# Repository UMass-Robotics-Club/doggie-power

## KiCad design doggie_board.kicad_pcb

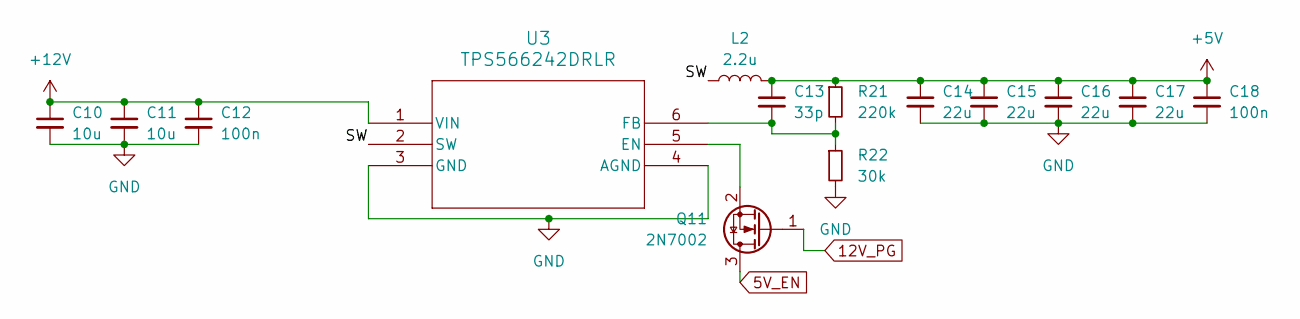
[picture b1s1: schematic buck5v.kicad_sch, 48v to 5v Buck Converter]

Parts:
C10, C11: 10u; C_0603_1608Metric_Pad1.08x0.95mm_HandSolder
C12, C18: 100n; C_0603_1608Metric_Pad1.08x0.95mm_HandSolder
C13: 33p; C_0603_1608Metric_Pad1.08x0.95mm_HandSolder
C14, C15, C16, C17: 22u; C_0603_1608Metric_Pad1.08x0.95mm_HandSolder
L2: 2.2u; IND_1217AS-H-2R2N=P3
Q11: 2N7002; SOT-23
R21: 220k; R_0603_1608Metric_Pad0.98x0.95mm_HandSolder
R22: 30k; R_0603_1608Metric_Pad0.98x0.95mm_HandSolder
U3: TPS566242DRLR; SOT5x3_DRL_TEX

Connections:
5V_EN: Q11.3 (D); also elsewhere on the board
12V_PG: Q11.1 (G); also elsewhere on the board
+5V: C13.1, C14.1, C15.1, C16.1, C17.1, C18.1, L2.2, R21.1; also elsewhere on the board
+12V: C10.1, C11.1, C12.1, U3.1 (VIN); also elsewhere on the board
/5v Buck Converter/SW: L2.1, U3.2 (SW)
GND: C10.2, C11.2, C12.2, C14.2, C15.2, C16.2, C17.2, C18.2, R22.2, U3.3 (GND), U3.4 (AGND); also elsewhere on the board
unnamed: Q11.2 (S), U3.5 (EN)
unnamed: C13.2, R21.2, R22.1, U3.6 (FB)

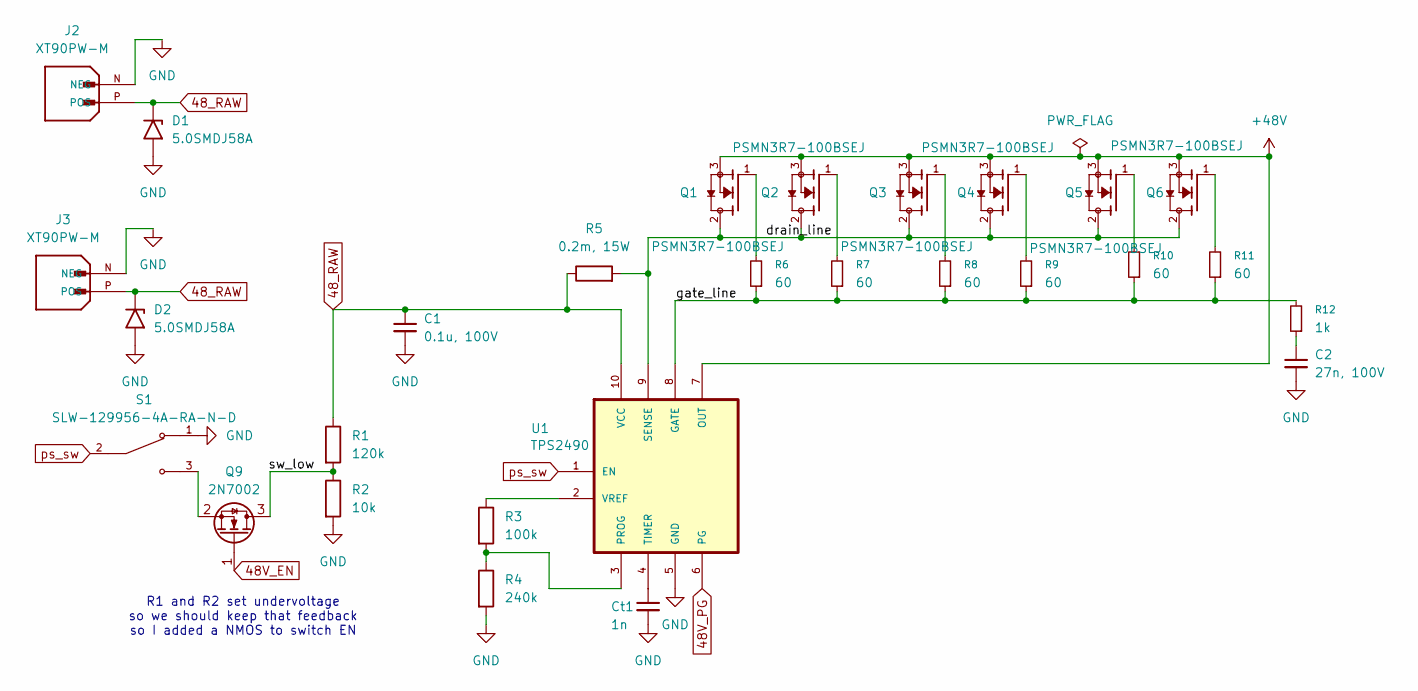
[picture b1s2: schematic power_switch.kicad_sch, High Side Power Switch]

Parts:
C1: 0.1u, 100V; C_0603_1608Metric_Pad1.08x0.95mm_HandSolder
C2: 27n, 100V; C_0603_1608Metric_Pad1.08x0.95mm_HandSolder
Ct1: 1n; C_0603_1608Metric_Pad1.08x0.95mm_HandSolder
D1, D2: 5.0SMDJ58A; D_SMB-SMC_Universal_Handsoldering
J2, J3: XT90PW-M; AMASS_XT90PW-M; PARTREV V00
Q1, Q2, Q3, Q4, Q5, Q6: PSMN3R7-100BSEJ; D2PAK_NEX; PARTREV 3 September 2018
Q9: 2N7002; SOT-23
R1: 120k; R_0603_1608Metric_Pad0.98x0.95mm_HandSolder
R2: 10k; R_0603_1608Metric_Pad0.98x0.95mm_HandSolder
R3: 100k; R_0603_1608Metric_Pad0.98x0.95mm_HandSolder
R4: 240k; R_0603_1608Metric_Pad0.98x0.95mm_HandSolder
R5: 0.2m, 15W; RES_PSR500_ROM
R6, R7, R8, R9, R10, R11: 60; R_0603_1608Metric_Pad0.98x0.95mm_HandSolder
R12: 1k; R_0603_1608Metric_Pad0.98x0.95mm_HandSolder
S1: SLW-129956-4A-RA-N-D; SW_SLW-129956-4A-RA-N-D; PARTREV 1.01
U1: TPS2490; VSSOP-10_3x3mm_P0.5mm

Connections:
48V_EN: Q9.1 (G); also elsewhere on the board
48V_PG: U1.6 (PG); also elsewhere on the board
48_RAW: C1.1, D1.1 (A1), D2.1 (A1), J2.P (POS), J3.P (POS), R1.1, R5.1, U1.10 (VCC); also elsewhere on the board
+48V: Q1.3, Q2.3, Q3.3, Q4.3, Q5.3, Q6.3, U1.7 (OUT); also elsewhere on the board
/High Side Power Switch/drain_line: Q1.2, Q2.2, Q3.2, Q4.2, Q5.2, Q6.2, R5.2, U1.9 (SENSE)
/High Side Power Switch/gate_line: R6.1, R7.1, R8.1, R9.1, R10.1, R11.1, R12.2, U1.8 (GATE)
/High Side Power Switch/sw_low: Q9.3 (D), R1.2, R2.1
GND: C1.2, C2.2, Ct1.2, D1.2 (A2), D2.2 (A2), J2.N (NEG), J3.N (NEG), R2.2, R4.2, S1.1, U1.5 (GND); also elsewhere on the board
unnamed: C2.1, R12.1
unnamed: Q1.1, R6.2
unnamed: Q2.1, R7.2
unnamed: Q3.1, R8.2
unnamed: Q4.1, R9.2
unnamed: Q5.1, R10.2
unnamed: Q6.1, R11.2
unnamed: Q9.2 (S), S1.3
unnamed: R3.2, R4.1, U1.3 (PROG)
unnamed: Ct1.1, U1.4 (TIMER)
unnamed: R3.1, U1.2 (VREF)
ps_sw: S1.2, U1.1 (EN)

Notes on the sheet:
R1 and R2 set undervoltage so we should keep that feedback so I added a NMOS to switch EN

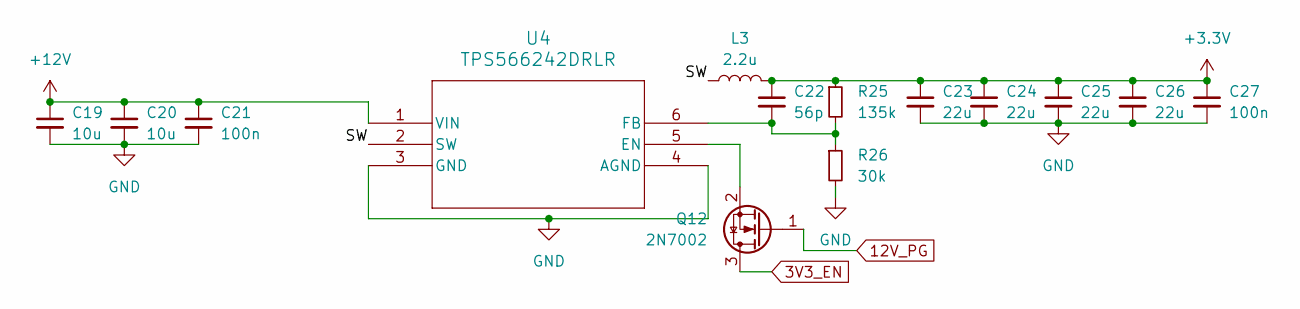
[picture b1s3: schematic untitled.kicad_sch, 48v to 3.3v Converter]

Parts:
C19, C20: 10u; C_0603_1608Metric_Pad1.08x0.95mm_HandSolder
C21, C27: 100n; C_0603_1608Metric_Pad1.08x0.95mm_HandSolder
C22: 56p; C_0603_1608Metric_Pad1.08x0.95mm_HandSolder
C23, C24, C25, C26: 22u; C_0603_1608Metric_Pad1.08x0.95mm_HandSolder
L3: 2.2u; IND_1217AS-H-2R2N=P3
Q12: 2N7002; SOT-23
R25: 135k; R_0603_1608Metric_Pad0.98x0.95mm_HandSolder
R26: 30k; R_0603_1608Metric_Pad0.98x0.95mm_HandSolder
U4: TPS566242DRLR; SOT5x3_DRL_TEX

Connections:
3V3_EN: Q12.3 (D); also elsewhere on the board
12V_PG: Q12.1 (G); also elsewhere on the board
+3.3V: C22.1, C23.1, C24.1, C25.1, C26.1, C27.1, L3.2, R25.1; also elsewhere on the board
+12V: C19.1, C20.1, C21.1, U4.1 (VIN); also elsewhere on the board
/3.3v Buck Converter/SW: L3.1, U4.2 (SW)
GND: C19.2, C20.2, C21.2, C23.2, C24.2, C25.2, C26.2, C27.2, R26.2, U4.3 (GND), U4.4 (AGND); also elsewhere on the board
unnamed: Q12.2 (S), U4.5 (EN)
unnamed: C22.2, R25.2, R26.1, U4.6 (FB)

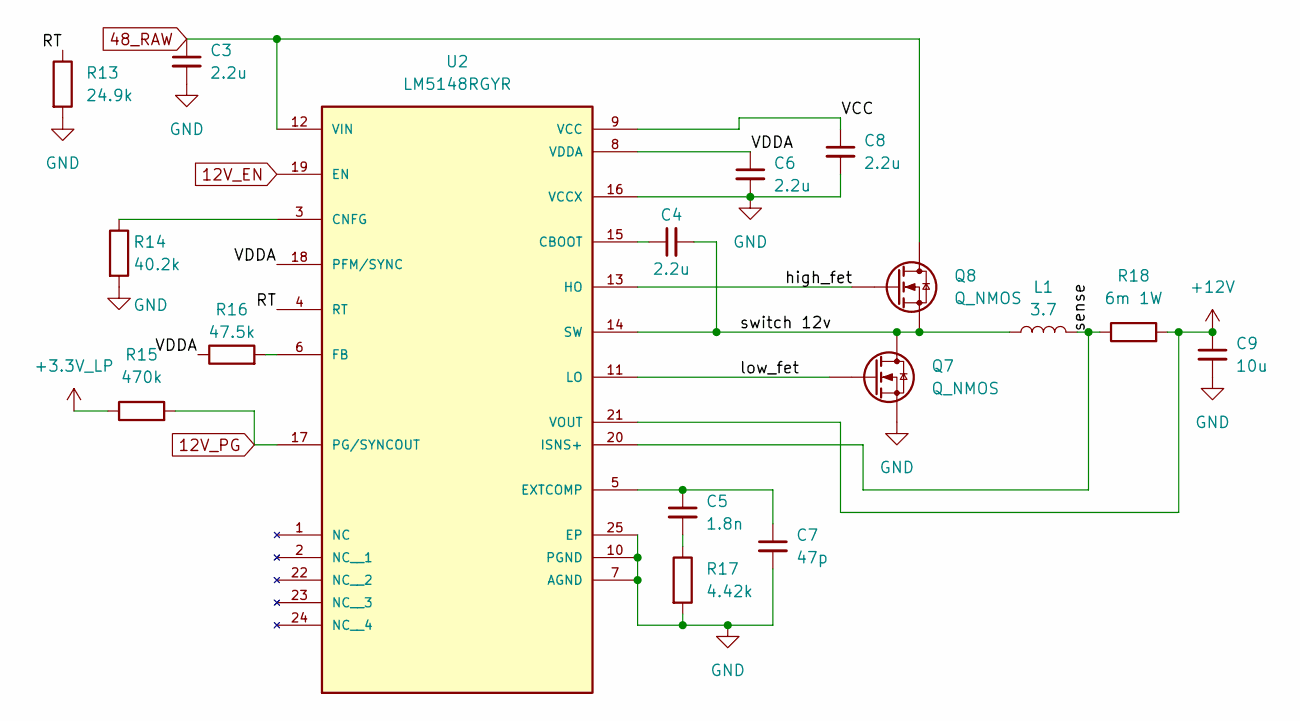
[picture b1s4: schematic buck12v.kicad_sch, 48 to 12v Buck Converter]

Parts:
C3, C4, C6, C8: 2.2u; C_0603_1608Metric_Pad1.08x0.95mm_HandSolder
C5: 1.8n; C_0603_1608Metric_Pad1.08x0.95mm_HandSolder
C7: 47p; C_0603_1608Metric_Pad1.08x0.95mm_HandSolder
C9: 10u; C_0603_1608Metric_Pad1.08x0.95mm_HandSolder
L1: 3.7; P1173.372NL
Q7, Q8: Q_NMOS; TO-252-2
R13: 24.9k; R_0603_1608Metric_Pad0.98x0.95mm_HandSolder
R14: 40.2k; R_0603_1608Metric_Pad0.98x0.95mm_HandSolder
R15: 470k; R_0603_1608Metric_Pad0.98x0.95mm_HandSolder
R16: 47.5k; R_0603_1608Metric_Pad0.98x0.95mm_HandSolder
R17: 4.42k; R_0603_1608Metric_Pad0.98x0.95mm_HandSolder
R18: 6m 1W; R_1206_3216Metric_Pad1.30x1.75mm_HandSolder
U2: LM5148RGYR; PARTEV February 2023

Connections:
12V_EN: U2.19 (EN); also elsewhere on the board
12V_PG: R15.2, U2.17 (PG/SYNCOUT); also elsewhere on the board
48_RAW: C3.1, Q8.2 (D), U2.12 (VIN); also elsewhere on the board
+3.3V_LP: R15.1; also elsewhere on the board
+12V: C9.1, R18.2, U2.21 (VOUT); also elsewhere on the board
/12v Buck Converter/RT: R13.1, U2.4 (RT)
/12v Buck Converter/VCC: C8.1, U2.9 (VCC)
/12v Buck Converter/VDDA: C6.1, R16.1, U2.8 (VDDA), U2.18 (PFM/SYNC)
/12v Buck Converter/high_fet: Q8.1 (G), U2.13 (HO)
/12v Buck Converter/low_fet: Q7.1 (G), U2.11 (LO)
/12v Buck Converter/sense: L1.2, R18.1, U2.20 (ISNS+)
/12v Buck Converter/switch 12v: C4.2, L1.1, Q7.2 (D), Q8.3 (S), U2.14 (SW)
GND: C3.2, C6.2, C7.2, C8.2, C9.2, Q7.3 (S), R13.2, R14.2, R17.2, U2.7 (AGND), U2.10 (PGND), U2.16 (VCCX), U2.25 (EP); also elsewhere on the board
unnamed: C5.2, R17.1
unnamed: C4.1, U2.15 (CBOOT)
unnamed: R14.1, U2.3 (CNFG)
unnamed: C5.1, C7.1, U2.5 (EXTCOMP)
unnamed: R16.2, U2.6 (FB)

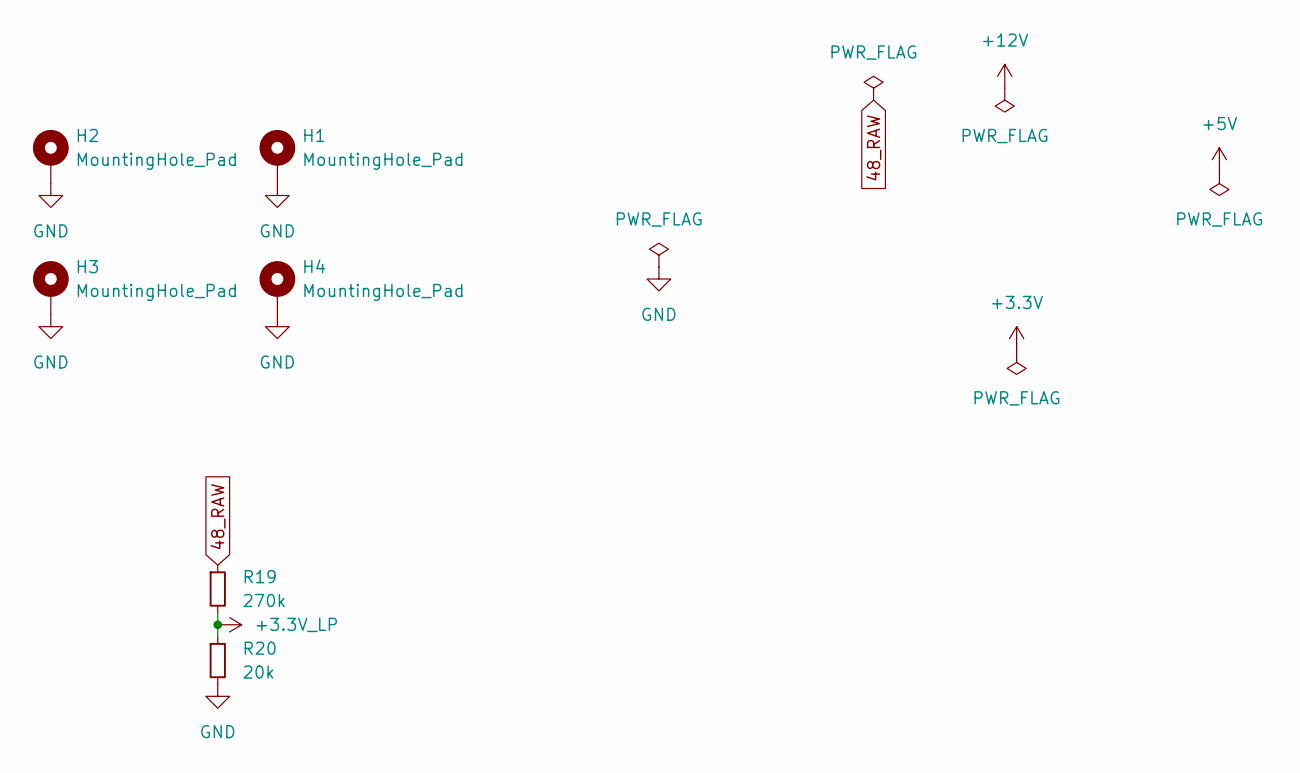
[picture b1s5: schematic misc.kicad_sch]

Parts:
H1, H2, H3, H4: MountingHole_Pad; MountingHole_3.2mm_M3_DIN965_Pad_TopBottom
R19: 270k; R_0603_1608Metric_Pad0.98x0.95mm_HandSolder
R20: 20k; R_0603_1608Metric_Pad0.98x0.95mm_HandSolder

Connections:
48_RAW: R19.1; also elsewhere on the board
+3.3V_LP: R19.2, R20.1; also elsewhere on the board
GND: H1.1, H2.1, H3.1, H4.1, R20.2; also elsewhere on the board

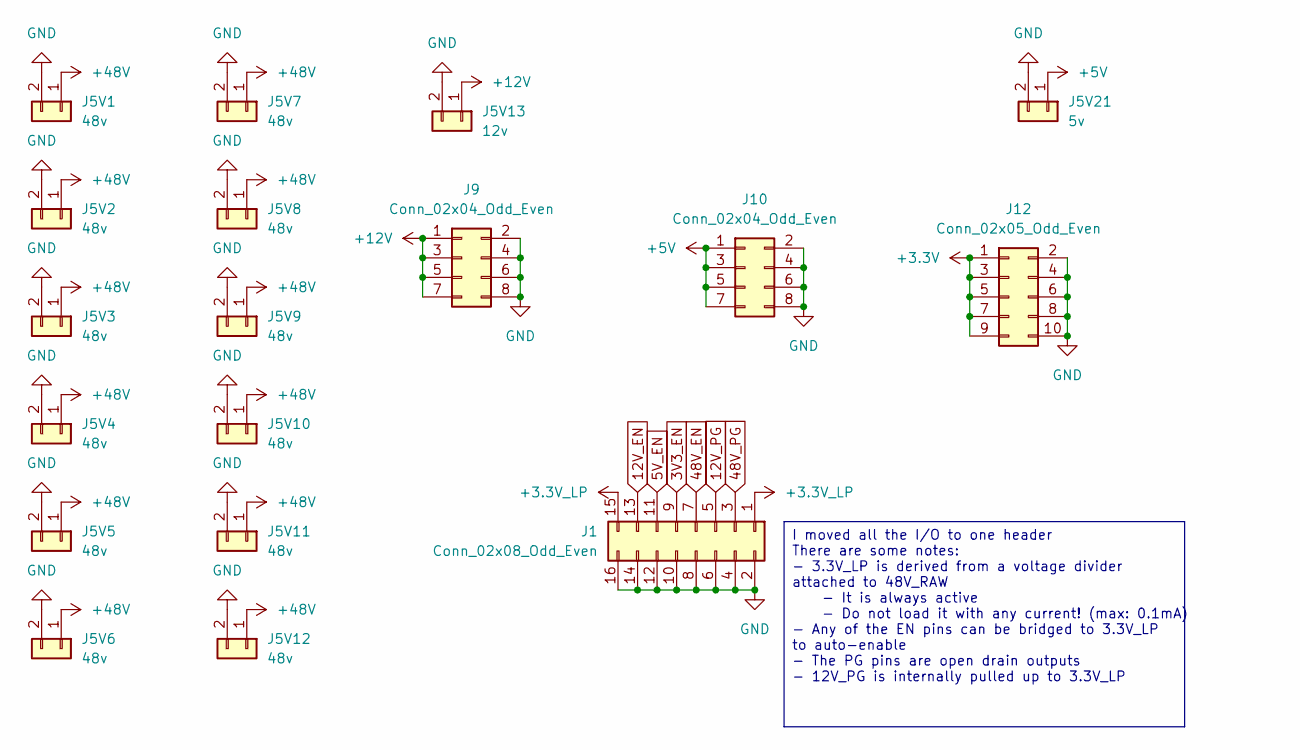
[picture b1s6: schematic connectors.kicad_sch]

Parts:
J1: Conn_02x08_Odd_Even; PinHeader_2x08_P2.54mm_Vertical
J5V1, J5V2, J5V3, J5V4, J5V5, J5V6, J5V7, J5V8, J5V9, J5V10, J5V11, J5V12: 48v; AMASS_XT30PW-M_1x02_P2.50mm_Horizontal
J5V13: 12v; CUI_PJ-037A
J5V21: 5v; CUI_PJ-037A
J9, J10: Conn_02x04_Odd_Even; PinHeader_2x04_P2.54mm_Vertical
J12: Conn_02x05_Odd_Even; PinHeader_2x05_P2.54mm_Vertical

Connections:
3V3_EN: J1.9; also elsewhere on the board
5V_EN: J1.11; also elsewhere on the board
12V_EN: J1.13; also elsewhere on the board
12V_PG: J1.5; also elsewhere on the board
48V_EN: J1.7; also elsewhere on the board
48V_PG: J1.3; also elsewhere on the board
+3.3V: J12.1, J12.3, J12.5, J12.7, J12.9; also elsewhere on the board
+3.3V_LP: J1.1, J1.15; also elsewhere on the board
+5V: J5V21.1, J10.1, J10.3, J10.5, J10.7; also elsewhere on the board
+12V: J5V13.1, J9.1, J9.3, J9.5, J9.7; also elsewhere on the board
+48V: J5V1.1, J5V2.1, J5V3.1, J5V4.1, J5V5.1, J5V6.1, J5V7.1, J5V8.1, J5V9.1, J5V10.1, J5V11.1, J5V12.1; also elsewhere on the board
GND: J1.2, J1.4, J1.6, J1.8, J1.10, J1.12, J1.14, J1.16, J5V1.2, J5V2.2, J5V3.2, J5V4.2, J5V5.2, J5V6.2, J5V7.2, J5V8.2, J5V9.2, J5V10.2, J5V11.2, J5V12.2, J5V13.2, J5V21.2, J9.2, J9.4, J9.6, J9.8, J10.2, J10.4, J10.6, J10.8, J12.2, J12.4, J12.6, J12.8, J12.10; also elsewhere on the board

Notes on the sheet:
I moved all the I/O to one header There are some notes: - 3.3V_LP is derived from a voltage divider attached to 48V_RAW - It is always active - Do not load it with any current! (max: 0.1mA) - Any of the EN pins can be bridged to 3.3V_LP to auto-enable - The PG pins are open drain outputs - 12V_PG i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

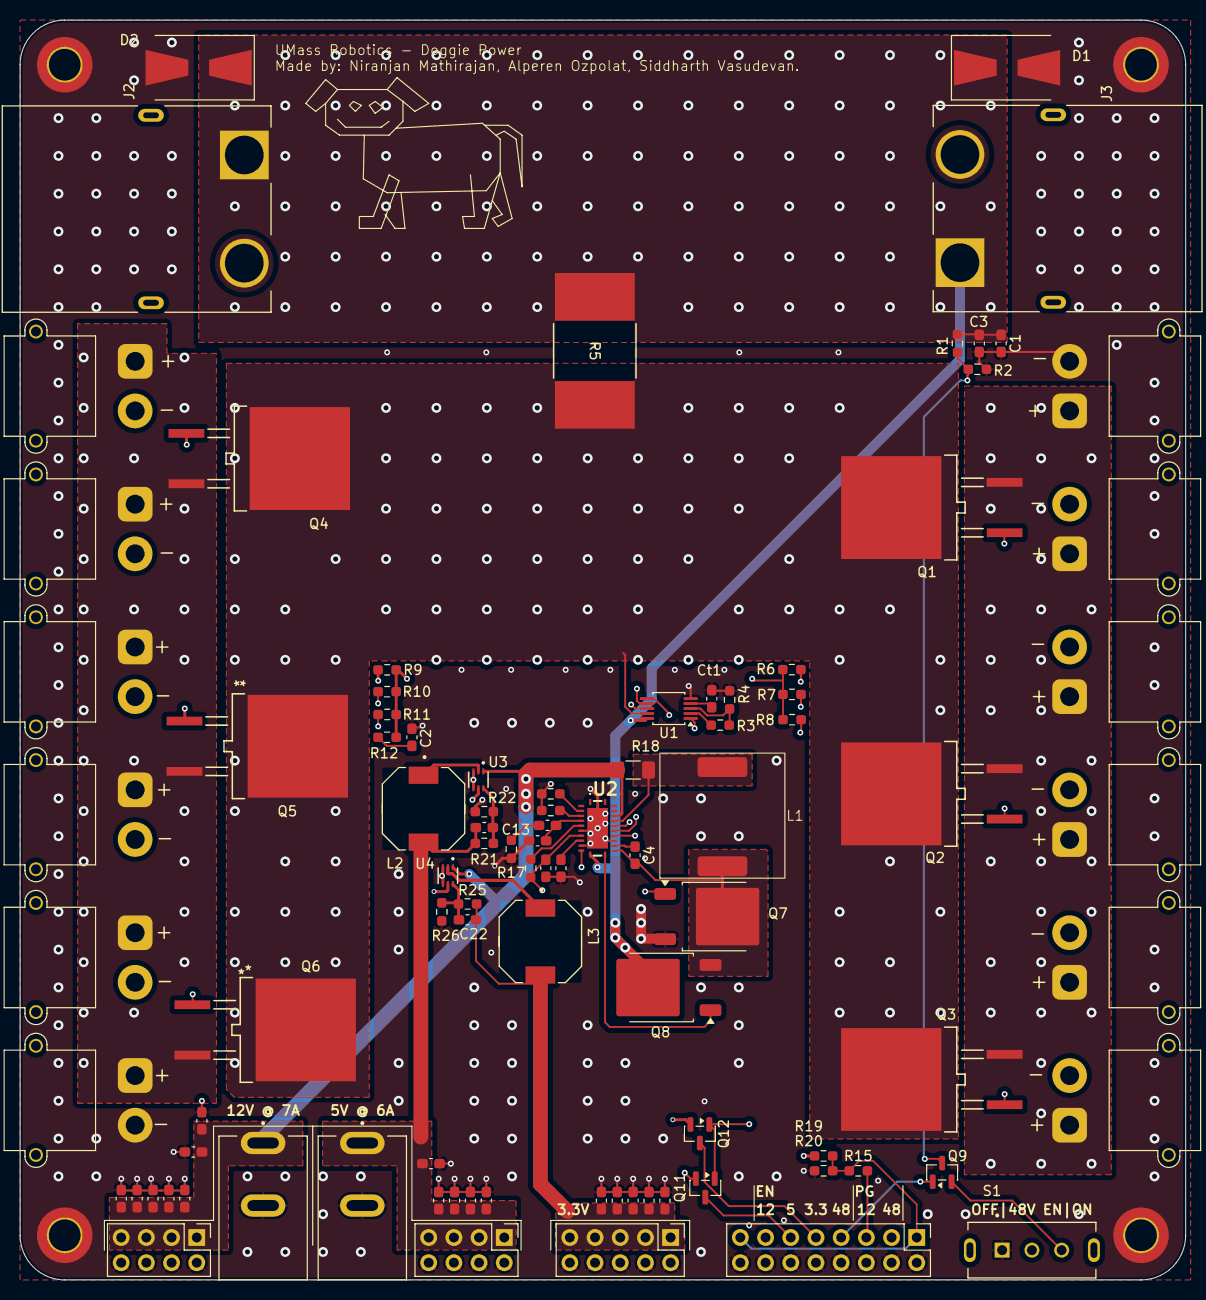
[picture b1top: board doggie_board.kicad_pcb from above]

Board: 4 copper layers, 117.5 x 127.0 mm, 97 parts (0 on the bottom side), 46 nets.

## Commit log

2025-10-20 initial hot swap controller
2025-10-28 Addition of Buck Converter
2025-11-18 Buck_Converter
    Ensure it was properly pushed
2025-11-24 feat: added power switch schematics
2025-11-24 added calculator
2026-02-04 fix nets
2026-02-04 cleaned up file structure
2026-02-04 feat: 48-5v buck converter
2026-02-05 Fixed ERC
    Created Buck3
2026-02-05 fixed ERC errors and footprint for the TPS2490
2026-02-05 Cleaned up repo, fixing naming
2026-02-05 fixed footprints
2026-02-05 fixed ERC
2026-02-09 moved schematics back to root folder
2026-02-10 3.3v linear converter
    added linear converter
2026-02-10 started routing
2026-02-12 Connectors Created
    Footprints added
2026-02-12 Connectors (fixed)
2026-02-12 progress on routing
2026-02-19 Renaming of Parts
    Rename
2026-02-19 updated footprints and pcb
2026-03-02 imported schematic
2026-03-03 routing progress
2026-03-04 transistor pins
2026-03-04 progress on right drain
2026-03-05 swapped left and right
2026-03-06 Fixed Schematics with more cost effective IC's
2026-03-07 feat: added footprints
2026-03-08 added headers and modified some stuff
2026-03-08 added footprints and standardized EN headers
2026-03-09 pcb routing
2026-03-11 additional progress on routing front copper
2026-03-15 march 14
2026-03-15 Mar14_11:45
2026-03-15 Mar15 4:20
2026-03-15 final push
2026-03-15 fix pads
2026-03-15 added spencer suggestion
2026-03-16 added my name
2026-03-16 om suggestions
2026-03-16 shortened board
2026-03-17 fixed clearances
2026-03-17 added switch and cleaned up board a little
2026-03-17 fixed footprintns
2026-03-17 fixed vias and added stitching
2026-03-17 added header labels
2026-03-18 aligned mounting holes and csr
2026-03-18 reordered names
2026-03-18 fixed mounting holes and added rounded corners
2026-03-18 fixed 3d models for xt30
2026-03-18 updated headers
2026-04-07 upadated board to use 2 power layers
2026-04-07 removed extra silkscreen
